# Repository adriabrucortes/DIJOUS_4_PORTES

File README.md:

View this project on [CADLAB.io](https://cadlab.io/project/27987). 

# Projecte Eines de Disseny - PORTES
#### Adrià Brú, Miquel Limón, Lluís Pujadas

## Especificacions/Components

| Type                          | Name                  | Datasheet                                                                                                                                                                                                                                                                                                                                                                                                                                          | Link                                                                                                                                                     | Price      |
| ----------------------------- | --------------------- | -------------------------------------------------------------------------------------------------------------------------------------------------------------------------------------------------------------------------------------------------------------------------------------------------------------------------------------------------------------------------------------------------------------------------------------------------- | -------------------------------------------------------------------------------------------------------------------------------------------------------- | ---------- |
| uC                            | PIC32MK0256MCJ048     | [uC](https://ww1.microchip.com/downloads/aemDocuments/documents/MCU32/ProductDocuments/DataSheets/PIC32MK-General-Purpose-and-Motor-Control-With-CAN-FD-Family-DataSheet-DS60001570D.pdf)                                                                                                                                                                                                                                                          | [Mouser](https://www.mouser.es/ProductDetail/Microchip-Technology/PIC32MK0256MCJ048-E-Y8X?qs=vmHwEFxEFR%2FV8wN%2Fdp0noA%3D%3D)                           | 7,37 €     |
| LDO 3.3V (3A)                 | LT1528CT#PBF          | [LDO](https://rocelec.widen.net/view/pdf/nbjrjihvdn/LITCS09222-1.pdf?t.download=true&u=5oefqw)                                                                                                                                                                                                                                                                                                                                                     | [Digikey](https://www.digikey.es/en/products/detail/rochester-electronics-llc/LT1528CT-PBF/13481919)                                                     | 5,75 €     |
| Motor (588Nm, 280mA)          | HG37-200-AA-00        | [motor](https://www.mouser.es/datasheet/2/972/hg37-2525173.pdf)                                                                                                                                                                                                                                                                                                                                                                                    | [Mouser](https://www.mouser.es/ProductDetail/Nidec-Components/HG37-200-AA-00?qs=Wj%2FVkw3K%252BMBRymxOaiVRvg%3D%3D)                                      | 26,74 €    |
| CAN Transciever               | TCAN3413DR            | [can](https://www.ti.com/lit/ds/symlink/tcan3414.pdf?ts=1711721678762&ref_url=https%253A%252F%252Fwww.mouser.it%252F)                                                                                                                                                                                                                                                                                                                              | [Mouser](https://www.mouser.es/ProductDetail/Texas-Instruments/TCAN3413DR?qs=sGAEpiMZZMuyKkoWRCJ2WCtyf8MLmt92v%252BoGH2%2F%2FnqAqFeWM6BEVrA%3D%3D)       | 2,41 €     |
| Crystal Osc                   | ECS-3225SMV-080-GP-TR | [clk](https://www.mouser.es/datasheet/2/122/ECS_3225SMV-1623609.pdf)                                                                                                                                                                                                                                                                                                                                                                               | [Mouser](https://www.mouser.es/ProductDetail/ECS/ECS-3225SMV-080-GP-TR?qs=sGAEpiMZZMtldj7qu1ydrbV2KlGvrVWIvUi3jDw2tLHT0SWfK9heCg%3D%3D)                  | 1,92 €     |
| Driver (3.5A, +csense)        | MAX22201ATC+          | [driver](https://www.mouser.es/datasheet/2/609/MAX22201_MAX22207-3127854.pdf)                                                                                                                                                                                                                                                                                                                                                                      | [Mouser](https://www.mouser.es/ProductDetail/Analog-Devices-Maxim-Integrated/MAX22201ATC%2b?qs=stqOd1AaK7%252Bdqi04%2FQHs9Q%3D%3D)                       | 1,56 €     |
| ~~Current sensor (75A)~~      | ~~TMCS1123B2AQDVGR~~  | ~~[csense](https://www.ti.com/lit/ds/symlink/tmcs1123.pdf?ts=1711707167099&ref_url=https%253A%252F%252Fwww.ti.com%252Fproduct%252FTMCS1123%253Futm_source%253Dgoogle%2526utm_medium%253Dcpc%2526utm_campaign%253Dasc-null-null-GPN_EN-cpc-pf-google-wwe_cons%2526utm_content%253DTMCS1123%2526ds_k%253DTMCS1123%2526DCM%253Dyes%2526gad_source%253D1%2526gclid%253DEAIaIQobChMIrdeOip6ZhQMVVSitBh03AwOFEAAYAiAAEgLiCfD_BwE%2526gclsrc%253Daw.ds)~~ | ~~[Mouser](https://www.mouser.es/ProductDetail/Texas-Instruments/TMCS1123B2AQDVGR?qs=sGAEpiMZZMsPDRSCoHb1X5I%2FjBVAAn8DJGrzHYBTAmBFitJQJPL%2Fbw%3D%3D)~~ | ~~5,63 €~~ |
| Zener 12V (150MW)             | DDZ9699T-7            | [zener](https://eu.mouser.com/datasheet/2/115/DIOD_S_A0003550665_1-2542209.pdf)                                                                                                                                                                                                                                                                                                                                                                    | [Mouser](https://eu.mouser.com/ProductDetail/Diodes-Incorporated/DDZ9699T-7?qs=mQbszxtPdlOBwg08InvD3Q%3D%3D)                                             | 0,41 €     |
| Díode                         | BYV10MX-600PQ         | [diode](https://eu.mouser.com/datasheet/2/848/BYV10MX_600P-2401273.pdf)                                                                                                                                                                                                                                                                                                                                                                            | [Mouser](https://eu.mouser.com/ProductDetail/WeEn-Semiconductors/BYV10MX-600PQ?qs=QNEnbhJQKvYwaGjd%2F4%252BPWg%3D%3D)                                    | 0,54 €     |
| RFID                          | DLP-RFID2             | [rfid](https://mm.digikey.com/Volume0/opasdata/d220001/medias/docus/5656/DLP-RFID2%28D%29-V2.pdf)                                                                                                                                                                                                                                                                                                                                                  | [Digikey](https://www.digikey.es/en/products/detail/dlp-design-inc/DLP-RFID2/3770244)                                                                    | 35,04 €    |
| Motor lineal (150N, 2A) (opc) | DLA-12-5-A-50-IP65    | [motor-lineal](https://www.transmotec.com/Download/Catalog/Transmotec-EN-DLA-2022.pdf)                                                                                                                                                                                                                                                                                                                                                             | [Transmotec](https://www.transmotec.com/product/dla-12-5-a-50-pot-ip65/)                                                                                 | 303,5 €    |
| Final de Carrera  (5V)        | ESE-22MV21T           | [Final-Carrera](https://industrial.panasonic.com/cdbs/www-data/pdf/ATB0000/ATB0000C12.pdf)                                                                                                                                                                                                                                                                                                                                                         | [Digikey](https://www.digikey.es/en/products/detail/panasonic-electronic-components/ESE-22MV21T/1245478)                                                 | 0,42 €     |
| DC/DC 5V (2A, +/-49.5mV)      | P7805-2000R-S         | [dcdc2A](https://eu.mouser.com/datasheet/2/670/p78_2000r_s-3070500.pdf)                                                                                                                                                                                                                                                                                                                                                                            | [Mouser](https://eu.mouser.com/ProductDetail/CUI-Inc/P7803-2000R-S?qs=vvQtp7zwQdObalelOc2Obw%3D%3D)                                                      | 5,53 €     |
| DC/DC 3.3V (3A, +/-33.3mV)    | P783-Q24-S3-S         | [dcdc3A](https://eu.mouser.com/datasheet/2/670/p783_s-1889817.pdf)                                                                                                                                                                                                                                                                                                                                                                                 | [Mouser](https://eu.mouser.com/ProductDetail/CUI-Inc/P783-Q24-S3-S?qs=sPbYRqrBIVl7G8uy4wpmww%3D%3D)                                                      | 15,07 €    |
| C Tan 1u 20V 3216-18          | T491A105K020AT4360    | [ctant1u](https://eu.mouser.com/datasheet/2/447/KEM_T2005_T491-3316937.pdf)                                                                                                                                                                                                                                                                                                                                                                        | [Mouser](https://eu.mouser.com/ProductDetail/KEMET/T491A105K020AT4360?qs=sGAEpiMZZMsh%252B1woXyUXjyEnHz%2F1kG1y%2Fw9r1ZBsrUs%3D)                         | 0,07 €     |
| C Cer 22u 10V 1206            | CL31B226KPHNNWE       | [cer22u](https://eu.mouser.com/datasheet/2/585/MLCC-1837944.pdf)                                                                                                                                                                                                                                                                                                                                                                                   | [Mouser](https://eu.mouser.com/ProductDetail/Samsung-Electro-Mechanics/CL31B226KPHNNWE?qs=xZ%2FP%252Ba9zWqYr7HUxVtf3Yw%3D%3D)                            | 0,086 €    |
| C Cer 22u 50V                 | KTS500B226M76N0T00    | [ccer22u50v](https://eu.mouser.com/datasheet/2/420/nipc_s_a0010886389_1-2285932.pdf)                                                                                                                                                                                                                                                                                                                                                               | [Mouser](https://eu.mouser.com/ProductDetail/Chemi-Con/KTS500B226M76N0T00?qs=yFwz03cOJpkGGSneI4ka0Q%3D%3D)                                               | 3,58 €     |
| C Cer 10n 25V 1206            | KAM31BR81H103KT       | [ccer10n50v](https://eu.mouser.com/datasheet/2/40/AutoMLCCKAM-3216307.pdf)                                                                                                                                                                                                                                                                                                                                                                         | [Mouser](https://eu.mouser.com/ProductDetail/KYOCERA-AVX/KAM31BR81H103KT?qs=Jm2GQyTW%2FbjzijSUJGW%2FJA%3D%3D)                                            | 0,28 €     |
| C Ele 4.7u 35V                | 865080540002          | [cele4.7u](https://www.we-online.com/components/products/datasheet/865080540002.pdf)                                                                                                                                                                                                                                                                                                                                                               | [Mouser](https://eu.mouser.com/ProductDetail/Wurth-Elektronik/865080540002?qs=sGAEpiMZZMsh%252B1woXyUXj4jKQI6sNRw6puNwow3HMPo%3D)                        | 0,17 €     |
| C Ele 47u 16V                 | 860010372004          | [cele74u](https://www.we-online.com/components/products/datasheet/860010372004.pdf)                                                                                                                                                                                                                                                                                                                                                                | [Mouser](https://www.mouser.es/ProductDetail/Wurth-Elektronik/860010372004?qs=sGAEpiMZZMsh%252B1woXyUXj4jKQI6sNRw6V%2FBdkDX4IUo%3D)                      | 0,09 €     |
| C Cer 1u 25V 0805             | C0805C105K3RAC        | [cer1u25v](https://www.mouser.es/datasheet/2/447/KEM_C1002_X7R_SMD-3316098.pdf)                                                                                                                                                                                                                                                                                                                                                                    | [Mouser](https://www.mouser.es/ProductDetail/KEMET/C0805C105K3RAC?qs=ycRbFa0SLRQpHhAu2LUs4g%3D%3D)                                                       | 0,021 €    |
| C Cer 0.1u 50V 0805           | C0805C104M5RAC        | [cer100n0805](https://eu.mouser.com/datasheet/2/447/KEM_C1002_X7R_SMD-3316098.pdf)                                                                                                                                                                                                                                                                                                                                                                 | [Mouser](https://eu.mouser.com/ProductDetail/KEMET/C0805C104M5RAC?qs=VOOUd%252Bza08rWzt4y8eXMuQ%3D%3D)                                                   | 0,008 €    |
| C Cer 21p 50V 01005           | GRM0225C1H210GA02L    | [cer21p01005](https://eu.mouser.com/datasheet/2/281/murata_03052018_GRM_Series_1-1310166.pdf)                                                                                                                                                                                                                                                                                                                                                      | [Mouser](https://eu.mouser.com/ProductDetail/Murata-Electronics/GRM0225C1H210GA02L?qs=qkDYIeTQ%252BEl6hnZ3ixEkiA%3D%3D)                                  | 0,09 €     |
| R 120 125mW 0805              | CQ05WAF1200T5E        | [r120](https://www.mouser.es/datasheet/2/1365/10-3358738.pdf)                                                                                                                                                                                                                                                                                                                                                                                      | [Mouser](https://www.mouser.es/ProductDetail/Royalohm/CQ05WAF1200T5E?qs=sGAEpiMZZMtlubZbdhIBINZaoL9yqB51WBf9LviuJYE%3D)                                  | 0,002 €    |
| R 1k 125mW 0805               | TC05W8F1001T5G        | [r1k](https://eu.mouser.com/datasheet/2/1365/21-3077223.pdf)                                                                                                                                                                                                                                                                                                                                                                                       | [Mouser](https://eu.mouser.com/ProductDetail/Royalohm/TC05W8F1001T5G?qs=ST9lo4GX8V0X3zBMraFh1A%3D%3D)                                                    | 0,007 €    |
| R 330 125mW 0805              | TC0550F3300T5F        | [r330](https://eu.mouser.com/datasheet/2/1365/21-3077223.pdf)                                                                                                                                                                                                                                                                                                                                                                                      | [Mouser](https://eu.mouser.com/ProductDetail/Royalohm/TC0550F3300T5F?qs=T%252BzbugeAwjgeSBQZlDaTmA%3D%3D)                                                | 0,007 €    |
| R 10k 0.25W 0805              | RNCP0805JTD10K0       | [r10k](https://eu.mouser.com/datasheet/2/385/SEI_rncp-3077653.pdf)                                                                                                                                                                                                                                                                                                                                                                                 | [Mouser](https://eu.mouser.com/ProductDetail/SEI-Stackpole/RNCP0805JTD10K0?qs=IPgv5n7u5QaJFxYpOecM6A%3D%3D)                                              | 0,007 €    |
| R 100k 125mW 0805             | TC0550F1003T5G        | [r100k](https://eu.mouser.com/datasheet/2/1365/Royalohm_09132021_9__Thin_Film_20200106-2580434.pdf)                                                                                                                                                                                                                                                                                                                                                | [Mouser](https://eu.mouser.com/ProductDetail/Royalohm/TC0550F1003T5G?qs=Wj%2FVkw3K%252BMBYxpaKle1zIA%3D%3D)                                              | 0,007 €    |
| R 33k 125mW 0805              | TC0550D3302T5G        | [r33k](https://eu.mouser.com/datasheet/2/1365/Royalohm_09132021_9__Thin_Film_20200106-2580434.pdf)                                                                                                                                                                                                                                                                                                                                                 | [Mouser](https://eu.mouser.com/ProductDetail/Royalohm/TC0550D3302T5G?qs=Wj%2FVkw3K%252BMB5M6MpcX7%252Byw%3D%3D)                                          | 0,008 €    |

## Diagrama de blocs

## To Do
- [x] Add buttons
- [x] Add power input protection
- [x] Add controls
- [x] Resize boxes to same size (diagram)
- [x] Change "targeta" to "targeta clauer"
- [x] Restructure schematic for simplicity
- [x] Add buttons to schematic
- [x] Add expression for R (ISENSE)
- [x] Change regulator to DC/DC (maybe + regulator)
- [x] PCB v1
- [x] Change 2nd crystal to 32kHz (instead of 8MHz)
- [x] Correct via errors (DRC)
- [x] Solve pcb model compatibility issues
- [x] Rearrange power components
- [x] Remove SPI
- [ ] Make budget for different production quantities
- [ ] Correct silkscreen

## Changelogs
### 03/04
- Schematic done
- Corrected block diagram
	- Added additional data
	- Deleted 12V LDO
	- Changed current sensor for integrated Driver+Sensor
 
### 04/04
- Swapped regulator for DC/DC
- Add expression for R (ISENSE)
- Change regulator to DC/DC (maybe + regulator)
- Restructure schematic for simplicity
- Added 1 extra bit for window control

### 05/04 
- Added all components
- PWR plane done (v1)

### 06/04
- Corrected PWR
- Started digital

### 08/04
- Corrected diagram
- Changed from DC/DC to DC/DC (5V) + LDO (3,3V)
- Change second Clk to 32kHz
- Delete JTAG
- Correct oscillator connections

### 09/04
- Preliminar PCB done
- Added name to file
  
### 10/04
- Solved DRC
- Added names to board

### 11/04
- Changed SMD capacitors to ceramic

### 13/04
- Rearranged microcontroller pins

### 14/04
- Rearranged PCB to reduce through-holes

### 16/04
- Rearranged power stage

### 17/04
- Switched decoupling capacitors to back layer

### 18/04
- Solve DRC errors,
- Restructure 
- Change decoupling capacitors to bottom layer
- Corrections suggested by Joan

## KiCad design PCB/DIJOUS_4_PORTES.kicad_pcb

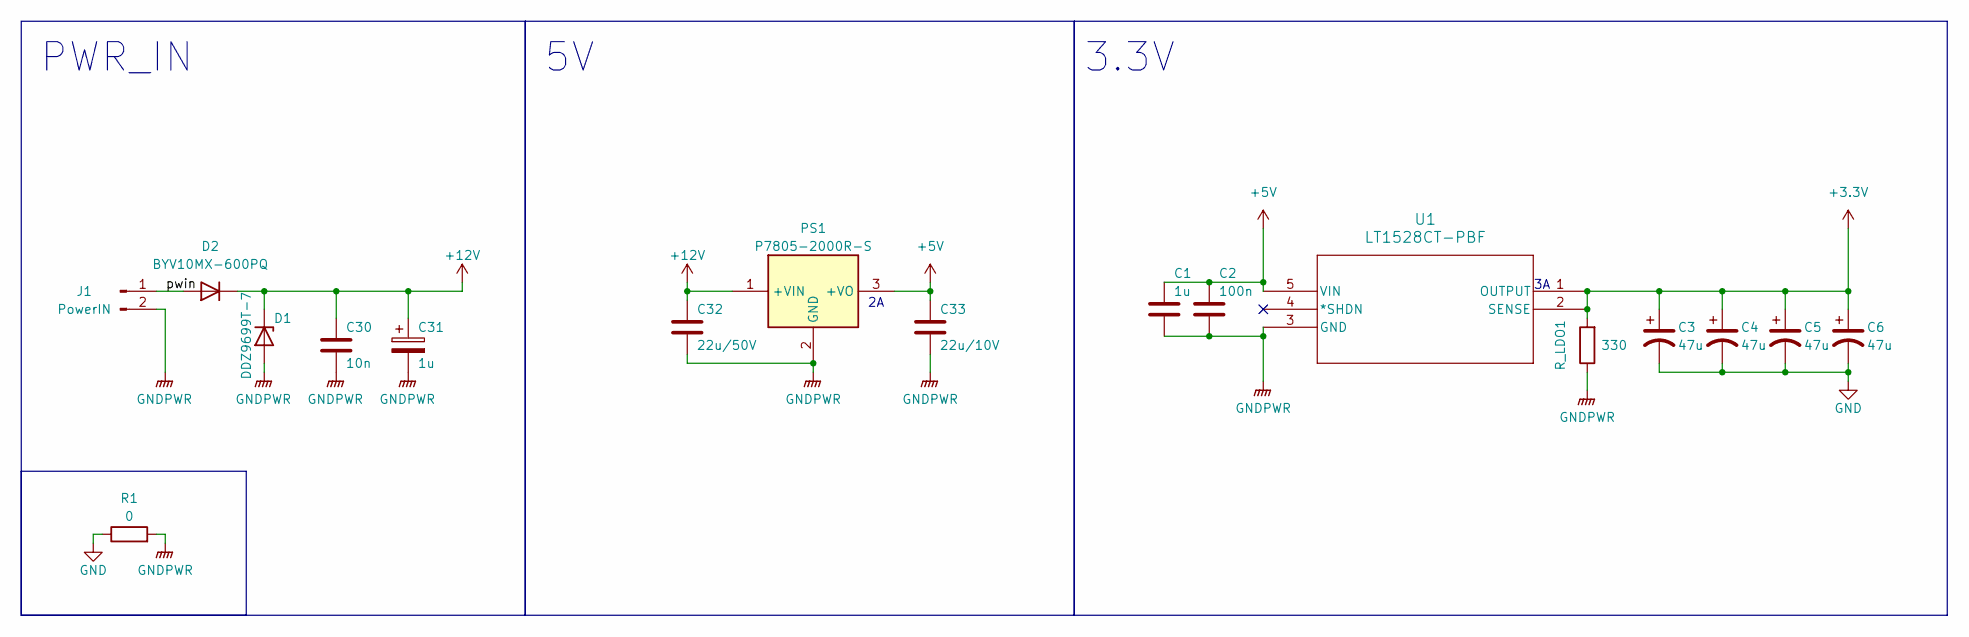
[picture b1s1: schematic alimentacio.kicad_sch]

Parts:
C1: 1u; C_0805_2012Metric
C2: 100n; C_0805_2012Metric
C3, C4, C5, C6: 47u; CP_Radial_D5.0mm_P2.00mm
C30: 10n; C_1206_3216Metric
C31: 1u; CP_EIA-3216-18_Kemet-A
C32: 22u/50V; CAPC7563X400N
C33: 22u/10V; C_1206_3216Metric
D1: DDZ9699T-7; SODFL1608X65N
D2: BYV10MX-600PQ; TO-220F-2_Horizontal_TabDown
J1: PowerIN; TerminalBlock_MetzConnect_Type011_RT05502HBWC_1x02_P5.00mm_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
PS1: P7805-2000R-S; P78032000RS; Manufacturer_Part_Number P7803-2000R-S
R1: 0
R_LDO1: 330; R_0805_2012Metric_Pad1.20x1.40mm_HandSolder
U1: LT1528CT-PBF; LT1528CT#PBF

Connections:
+3.3V: C3.1, C4.1, C5.1, C6.1, R_LDO1.2, U1.1 (OUTPUT), U1.2 (SENSE); also elsewhere on the board
+5V: C1.1, C2.1, C33.1, PS1.3 (+VO), U1.5 (VIN)
+12V: C30.1, C31.1, C32.1, D1.1 (K), D2.1 (K), PS1.1 (+VIN); also elsewhere on the board
/PWR IN/pwin: D2.2 (A), J1.1
GND: C3.2, C4.2, C5.2, C6.2, R1.1; also elsewhere on the board
GNDPWR: C1.2, C2.2, C30.2, C31.2, C32.2, C33.2, D1.2 (A), J1.2, PS1.2 (GND), R1.2, R_LDO1.1, U1.3 (GND); also elsewhere on the board

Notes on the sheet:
PWR_IN
3.3V

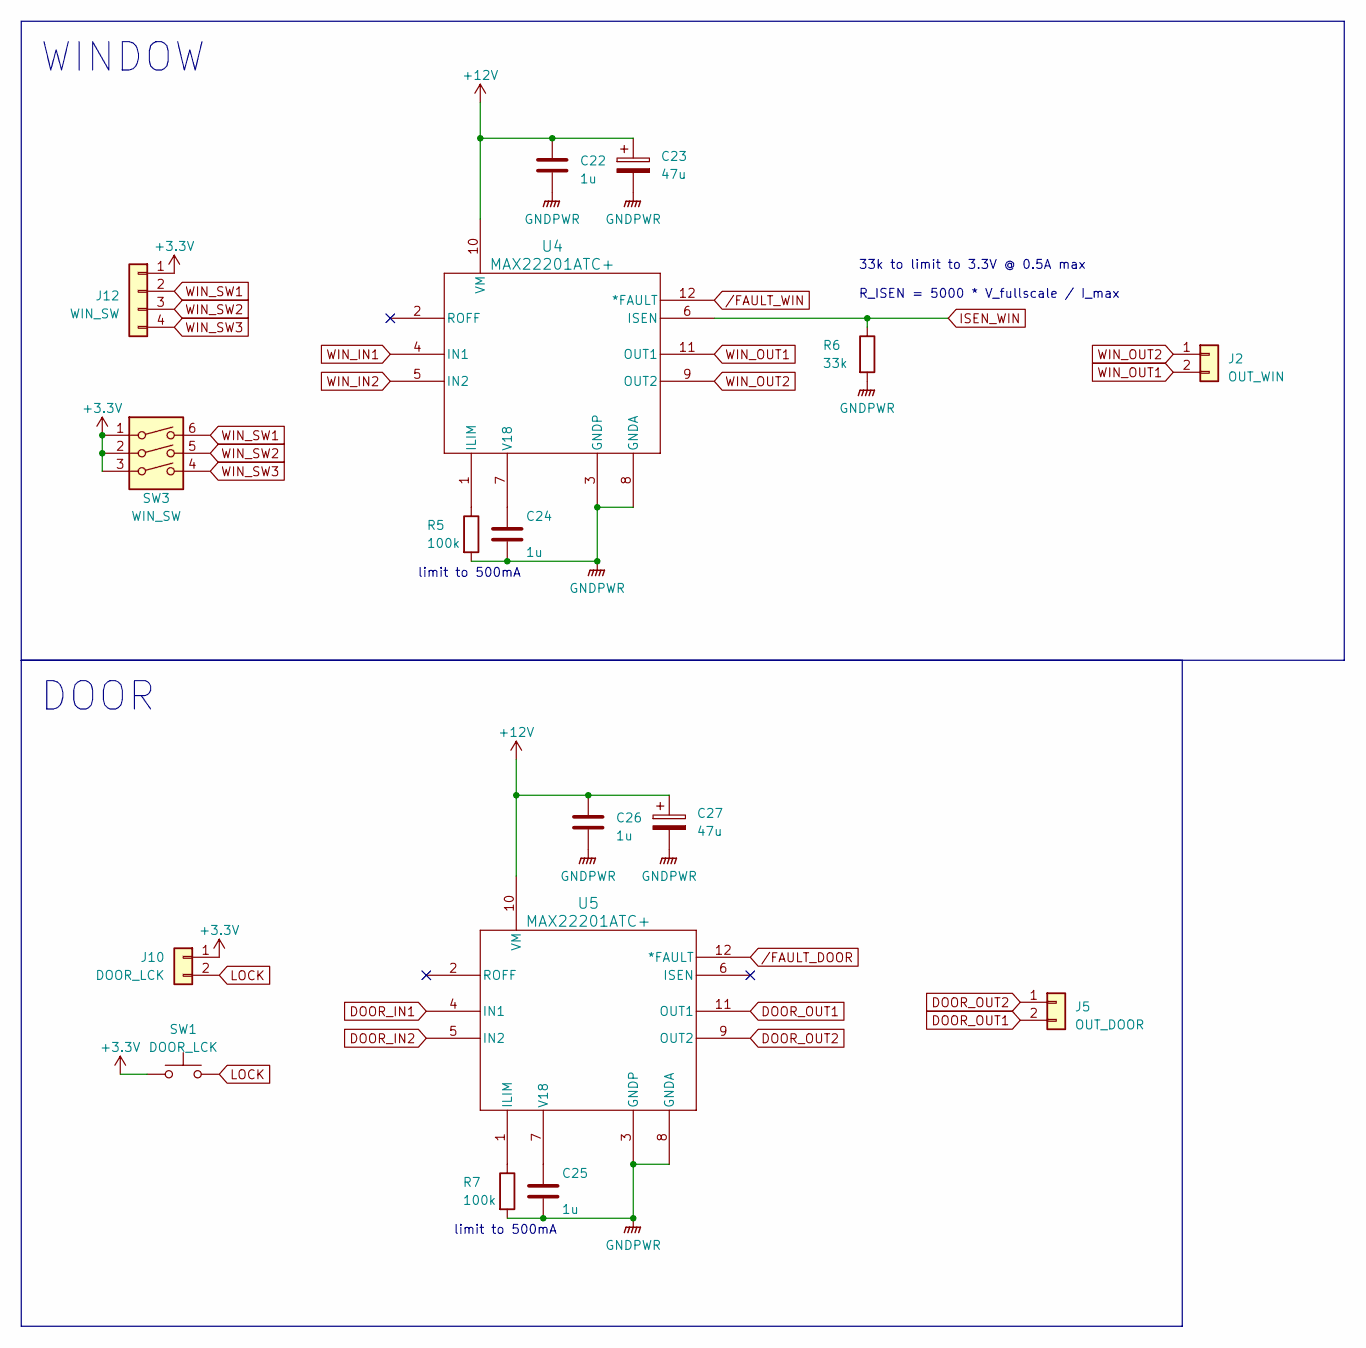
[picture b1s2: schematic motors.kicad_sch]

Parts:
C22, C24, C25, C26: 1u; C_0805_2012Metric
C23, C27: 47u; CP_Radial_D5.0mm_P2.00mm
J2: OUT_WIN; TerminalBlock_MetzConnect_Type011_RT05502HBWC_1x02_P5.00mm_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
J5: OUT_DOOR; TerminalBlock_MetzConnect_Type011_RT05502HBWC_1x02_P5.00mm_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
J10: DOOR_LCK; TerminalBlock_MetzConnect_Type011_RT05502HBWC_1x02_P5.00mm_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
J12: WIN_SW; TerminalBlock_MetzConnect_Type011_RT05504HBWC_1x04_P5.00mm_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
R5, R7: 100k; R_0805_2012Metric
R6: 33k; R_0805_2012Metric
SW1: DOOR_LCK; SW_CW_GPTS203211B
SW3: WIN_SW; SW_DIP_SPSTx03_Slide_6.7x9.18mm_W8.61mm_P2.54mm_LowProfile
U4, U5: MAX22201ATC+; MAX22201ATC_

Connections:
+3.3V: J10.1, J12.1, SW1.1, SW3.1, SW3.2, SW3.3; also elsewhere on the board
+12V: C22.1, C23.1, C26.1, C27.1, U4.10 (VM), U5.10 (VM); also elsewhere on the board
DOOR_IN1: U5.4 (IN1); also elsewhere on the board
DOOR_IN2: U5.5 (IN2); also elsewhere on the board
DOOR_OUT1: J5.2, U5.11 (OUT1)
DOOR_OUT2: J5.1, U5.9 (OUT2)
GNDPWR: C22.2, C23.2, C24.2, C25.2, C26.2, C27.2, R5.2, R6.2, R7.2, U4.3 (GNDP), U4.8 (GNDA), U5.3 (GNDP), U5.8 (GNDA); also elsewhere on the board
ISEN_WIN: R6.1, U4.6 (ISEN); also elsewhere on the board
LOCK: J10.2, SW1.2; also elsewhere on the board
unnamed: R5.1, U4.1 (ILIM)
unnamed: C24.1, U4.7 (V18)
unnamed: R7.1, U5.1 (ILIM)
unnamed: C25.1, U5.7 (V18)
WIN_IN1: U4.4 (IN1); also elsewhere on the board
WIN_IN2: U4.5 (IN2); also elsewhere on the board
WIN_OUT1: J2.2, U4.11 (OUT1)
WIN_OUT2: J2.1, U4.9 (OUT2)
WIN_SW1: J12.2, SW3.6; also elsewhere on the board
WIN_SW2: J12.3, SW3.5; also elsewhere on the board
WIN_SW3: J12.4, SW3.4; also elsewhere on the board
/FAULT_DOOR: U5.12 (*FAULT); also elsewhere on the board
/FAULT_WIN: U4.12 (*FAULT); also elsewhere on the board

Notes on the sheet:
DOOR
WINDOW
33k to limit to 3.3V @ 0.5A max R_ISEN = 5000 * V_fullscale / I_max
limit to 500mA

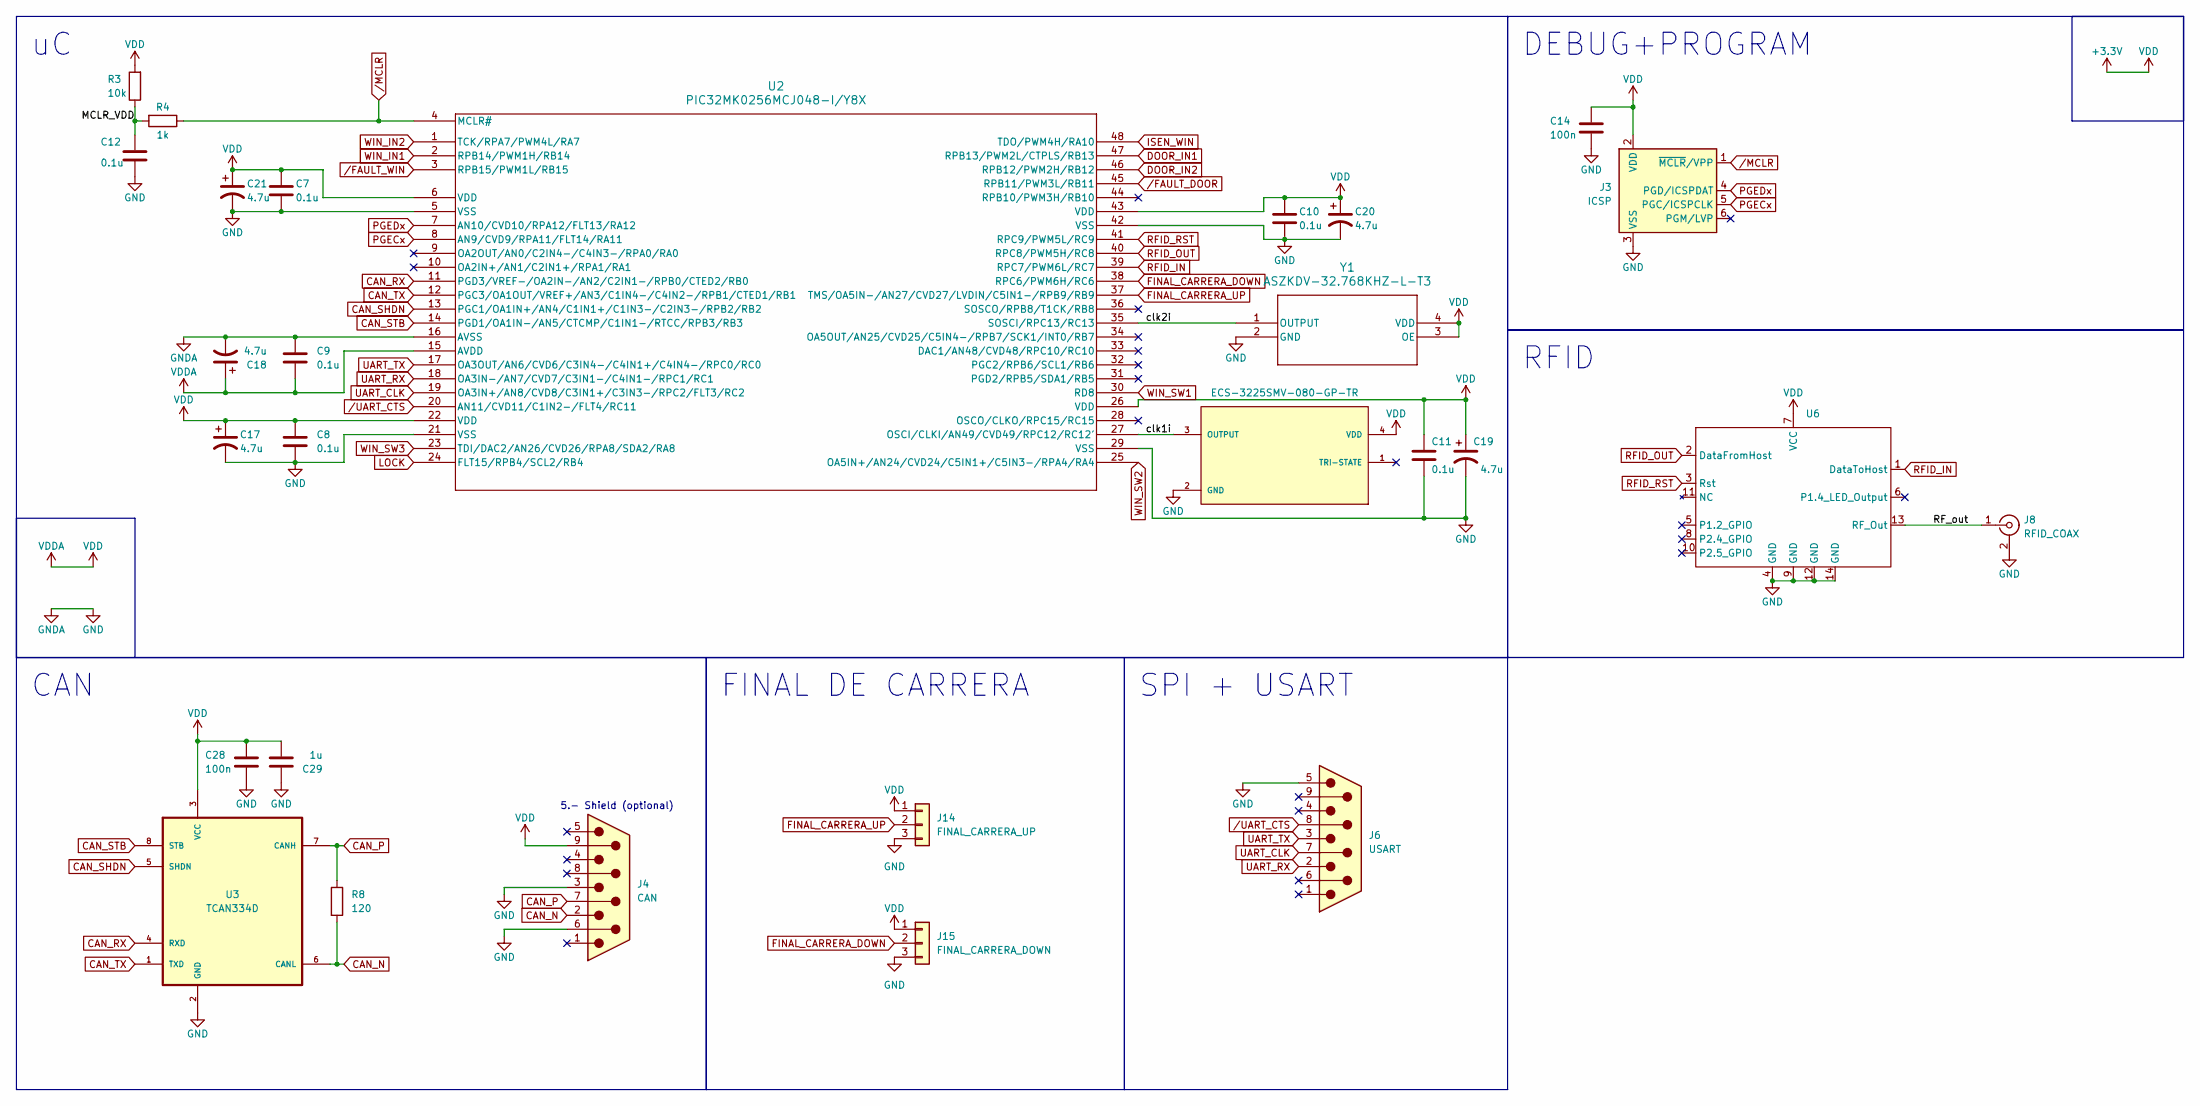
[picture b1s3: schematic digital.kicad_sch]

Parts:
C7, C8, C9, C10, C11, C12: 0.1u; C_0402_1005Metric
C14, C28: 100n; C_0402_1005Metric
C17, C18, C19, C20, C21: 4.7u; C_0805_2012Metric
C29: 1u; C_0402_1005Metric
J3: ICSP; PinHeader_1x06_P2.54mm_Vertical
J4: CAN; DSUB-9_Male_Horizontal_P2.77x2.84mm_EdgePinOffset4.94mm_Hou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
J6: USART; DSUB-9_Male_Horizontal_P2.77x2.84mm_EdgePinOffset4.94mm_Hou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
J8: RFID_COAX; BNC_TEConnectivity_1478035_Horizontal
J14: FINAL_CARRERA_UP; TerminalBlock_MetzConnect_Type011_RT05503HBWC_1x03_P5.00mm_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
J15: FINAL_CARRERA_DOWN; TerminalBlock_MetzConnect_Type011_RT05503HBWC_1x03_P5.00mm_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
R3: 10k; R_0805_2012Metric
R4: 1k; R_0805_2012Metric
R8: 120; R_0805_2012Metric
U2: PIC32MK0256MCJ048-I/Y8X; PIC32MK0256MCJ048-I-Y8X_MCH
U3: TCAN334D; TCAN3413DR
U6: DLP-RFID2
Y1: ASZKDV-32.768KHZ-L-T3; ASZKDV_ABR
Y2: ECS-3225SMV-080-GP-TR; OSC_ECS-3225SMV-080-GP-TR

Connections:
+3.3V: C7.1, C8.1, C9.2, C10.1, C11.1, C14.2, C17.1, C18.1, C19.1, C20.1, C21.1, C28.2, C29.1, J3.2 (VDD), J4.9, J14.1, J15.1, R3.2, U2.6 (VDD), U2.15 (AVDD), U2.22 (VDD), U2.26 (VDD), U2.43 (VDD), U3.3 (VCC), U6.7 (VCC), Y1.3 (OE), Y1.4 (VDD), Y2.4 (VDD); also elsewhere on the board
/DIGITAL/MCLR_VDD: C12.1, R3.1, R4.2
/DIGITAL/RF_out: J8.1 (In), U6.13 (RF_Out)
/DIGITAL/clk1i: U2.27 (OSCI/CLKI/AN49/CVD49/RPC12/RC12'), Y2.3 (OUTPUT)
/DIGITAL/clk2i: U2.35 (SOSCI/RPC13/RC13), Y1.1 (OUTPUT)
CAN_N: J4.2, R8.2, U3.6 (CANL)
CAN_P: J4.7, R8.1, U3.7 (CANH)
CAN_RX: U2.11 (PGD3/VREF-/OA2IN-/AN2/C2IN1-/RPB0/CTED2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), U3.4 (RXD)
CAN_SHDN: U2.13 (PGC1/OA1IN+/AN4/C1IN1+/C1IN3-/C2IN3-/RP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), U3.5 (SHDN)
CAN_STB: U2.14 (PGD1/OA1IN-/AN5/CTCMP/C1IN1-/RTCC/RPB3/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), U3.8 (STB)
CAN_TX: U2.12 (PGC3/OA1OUT/VREF+/AN3/C1IN4-/C4IN2-/RPB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), U3.1 (TXD)
DOOR_IN1: U2.47 (RPB13/PWM2L/CTPLS/RB13); also elsewhere on the board
DOOR_IN2: U2.46 (RPB12/PWM2H/RB12); also elsewhere on the board
FINAL_CARRERA_DOWN: J15.2, U2.38 (RPC6/PWM6H/RC6)
FINAL_CARRERA_UP: J14.2, U2.37 (TMS/OA5IN-/AN27/CVD27/LVDIN/C5IN1-/RPB9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)
GND: C7.2, C8.2, C9.1, C10.2, C11.2, C12.2, C14.1, C17.2, C18.2, C19.2, C20.2, C21.2, C28.1, C29.2, J3.3 (VSS), J4.3, J4.6, J6.5, J8.2 (Ext), J14.3, J15.3, U2.5 (VSS), U2.16 (AVSS), U2.21 (VSS), U2.29 (VSS), U2.42 (VSS), U3.2 (GND), U6.4 (GND), U6.9 (GND), U6.12 (GND), U6.14 (GND), Y1.2 (GND), Y2.2 (GND); also elsewhere on the board
ISEN_WIN: U2.48 (TDO/PWM4H/RA10); also elsewhere on the board
LOCK: U2.24 (FLT15/RPB4/SCL2/RB4); also elsewhere on the board
PGECx: J3.5 (PGC/ICSPCLK), U2.8 (AN9/CVD9/RPA11/FLT14/RA11)
PGEDx: J3.4 (PGD/ICSPDAT), U2.7 (AN10/CVD10/RPA12/FLT13/RA12)
RFID_IN: U2.39 (RPC7/PWM6L/RC7), U6.1 (DataToHost)
RFID_OUT: U2.40 (RPC8/PWM5H/RC8), U6.2 (DataFromHost)
RFID_RST: U2.41 (RPC9/PWM5L/RC9), U6.3 (Rst)
UART_CLK: J6.7, U2.19 (OA3IN+/AN8/CVD8/C3IN1+/C3IN3-/RPC2/FLT3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)
UART_RX: J6.2, U2.18 (OA3IN-/AN7/CVD7/C3IN1-/C4IN1-/RPC1/RC1)
UART_TX: J6.3, U2.17 (OA3OUT/AN6/CVD6/C3IN4-/C4IN1+/C4IN4-/RP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)
WIN_IN1: U2.2 (RPB14/PWM1H/RB14); also elsewhere on the board
WIN_IN2: U2.1 (TCK/RPA7/PWM4L/RA7); also elsewhere on the board
WIN_SW1: U2.30 (RD8); also elsewhere on the board
WIN_SW2: U2.25 (OA5IN+/AN24/CVD24/C5IN1+/C5IN3-/RPA4/RA4); also elsewhere on the board
WIN_SW3: U2.23 (TDI/DAC2/AN26/CVD26/RPA8/SDA2/RA8); also elsewhere on the board
/FAULT_DOOR: U2.45 (RPB11/PWM3L/RB11); also elsewhere on the board
/FAULT_WIN: U2.3 (RPB15/PWM1L/RB15); also elsewhere on the board
/MCLR: J3.1 (~MCLR/VPP), R4.1, U2.4 (MCLR#)
/UART_CTS: J6.8, U2.20 (AN11/CVD11/C1IN2-/FLT4/RC11)

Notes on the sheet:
5.- Shield (optional)
CAN
RFID
FINAL DE CARRERA
SPI + USART
DEBUG+PROGRAM

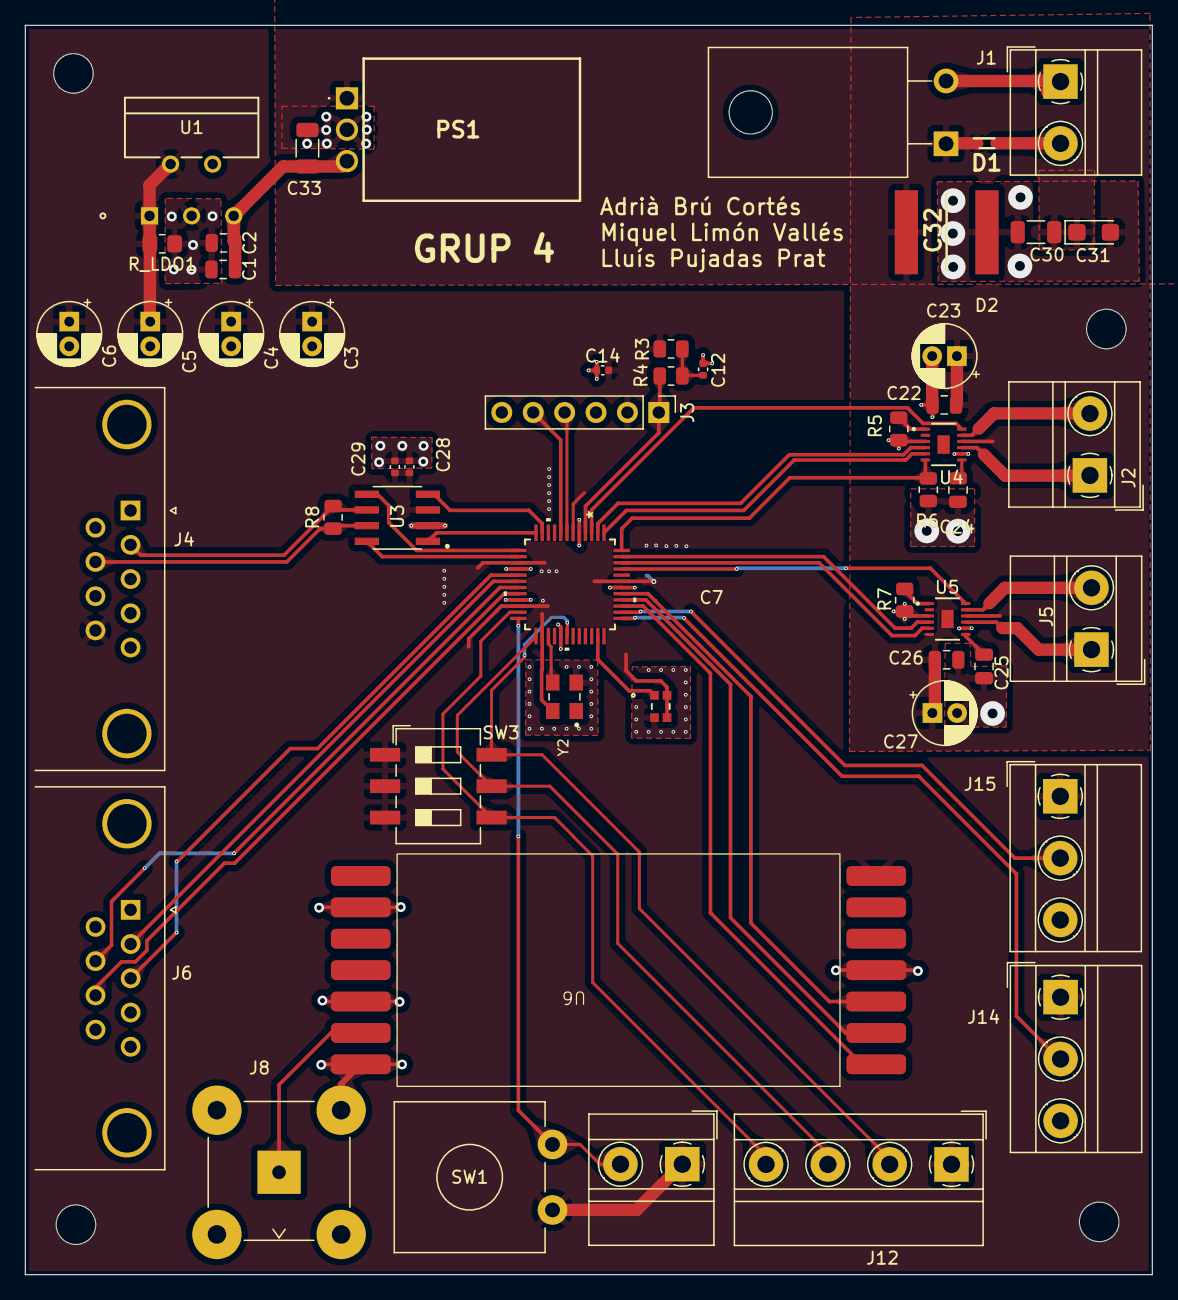
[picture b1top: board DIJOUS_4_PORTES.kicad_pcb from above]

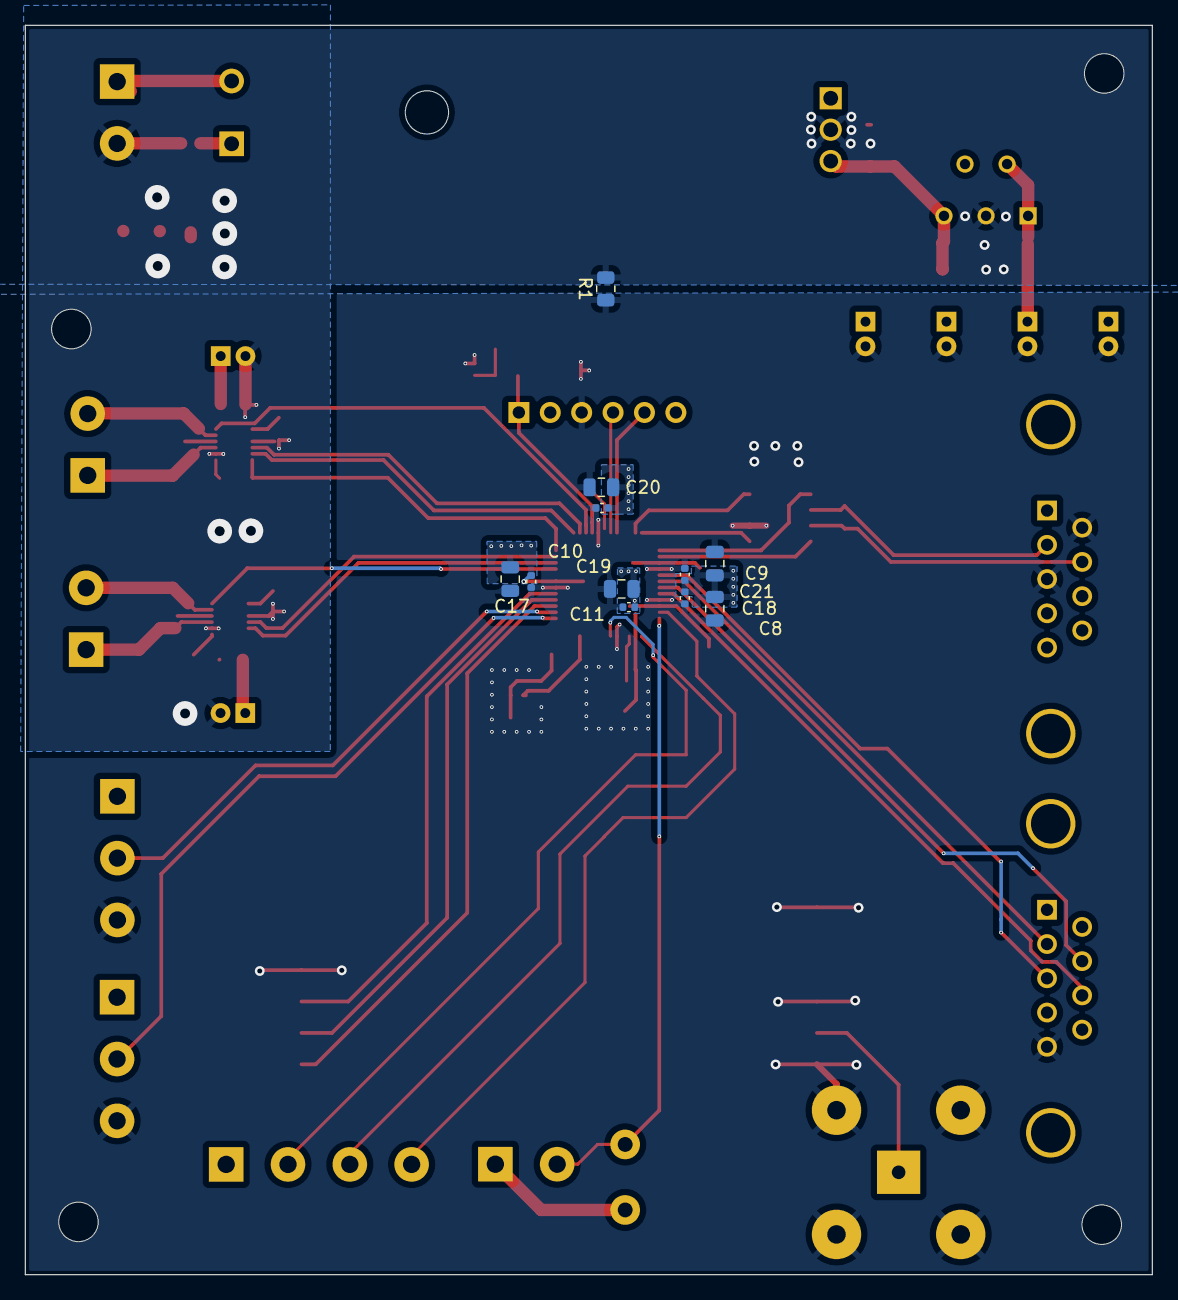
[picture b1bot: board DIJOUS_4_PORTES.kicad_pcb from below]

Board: 2 copper layers, 91.2 x 101.1 mm, 62 parts (11 on the bottom side), 47 nets.

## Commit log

2024-03-29 list v1
2024-03-29 list v2
2024-03-29 add space
2024-03-29 change LDO
2024-03-29 change links
2024-03-29 add models
2024-03-30 schematic wip
2024-03-31 falta RFID i final de carrera
2024-03-31 change RX to TX error
2024-04-02 prepare for shift
2024-04-02 DiagramaBlocs.drawio
2024-04-02 Agregado DiagramaBlocs.drawio
2024-04-02 Actualizar DiagramaBlocs.drawio
2024-04-02 add svg
2024-04-02 Actualizar DiagramaBlocs.drawio.svg
2024-04-02 test svg
2024-04-02 Backlink to CADLAB.io has been added.
2024-04-02 test png
2024-04-02 correct png
2024-04-02 guatafac cadlab
2024-04-02 guatafac cadlab v2
2024-04-02 flipant
2024-04-02 Actualizar Diagrama.png
2024-04-02 flipant pero funciona
2024-04-03 correct schematic + README
2024-04-03 add button controls
2024-04-04 sparse changes
2024-04-04 change file structure
2024-04-04 add current to linear actuator
2024-04-04 add TODOs
2024-04-04 update extra todos
2024-04-04 changed to DCDC 3.3V, added extra bit for window ctrl + misc corrections
2024-04-04 added all components
2024-04-04 power plane done
2024-04-05 Diagrama Modificat
2024-04-06 start digital
2024-04-08 Diagrama amb DC/DC
2024-04-08 Diagrama amb DC/DC ara si xd
2024-04-08 added LDO from DC/DC
2024-04-08 changed clks, pwr
2024-04-09 canvis a sortides de potencia
2024-04-09 xtra
2024-04-09 correcció missclick capacitat
2024-04-09 netclasses esquematic
2024-04-09 Netclasses Layout i canvis de GNDPWR a GND al layout d'alimentació
2024-04-10 first PCB done, need to correct vias and solve all DRC errors
2024-04-10 correccions diverses
2024-04-10 correccions de pista
2024-04-10 canvis i arreglos
2024-04-10 Solució d'errors DRC
2024-04-10 Add files via upload
    Arreglat DRC i afegit noms
2024-04-10 Arreglat DRC i afegit noms
2024-04-10 matrius de gnd
2024-04-15 PCB LAYOUT 2.0 - rearranged uc pins, changed smd Cs to ceramic
2024-04-17 PCB versió2
2024-04-18 arreglos
2024-04-18 definitivament es culpa del cadlab
2024-04-18 small readme update
2024-04-18 arreglo
2024-04-18 correccions joan
2024-04-18 parell diferencial
2024-04-18 excel components
2024-04-18 separate planes
2024-04-18 repareishons
2024-04-18 excel pressupost
2024-04-22 Resistències modificades a l'excel
2024-04-22 .\.git\
2024-04-24 Excel 50xpcb
2024-04-24 Ara si
2024-04-24 Pressupost 1000x i 20000x
2024-04-24 complete budget
2024-04-25 updated budget
2024-04-25 alguna cosa
2024-04-25 correcio pressupost
2024-04-25 gràfics gut
2024-04-25 updated presentation, added graphs
2024-04-25 corregir mida
